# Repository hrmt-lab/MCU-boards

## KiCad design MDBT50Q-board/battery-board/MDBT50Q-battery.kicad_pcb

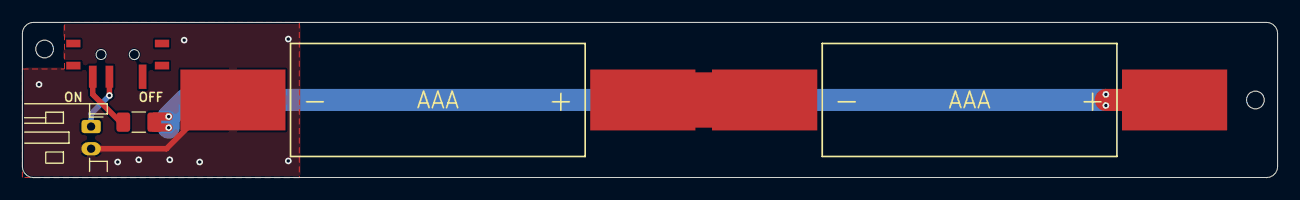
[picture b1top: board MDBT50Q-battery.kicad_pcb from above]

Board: 2 copper layers, 113.3 x 14.0 mm, 9 parts (0 on the bottom side), 5 nets.

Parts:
BT1, BT3: AAA-; BatteryClip_MYOUNG_MY-AAA-19-J
BT2, BT4: AAA+; BatteryClip_MYOUNG_MY-AAA-20-J
F1: 1206L075SLYR; Fuse_1206_3216Metric
H7, H8: M1.4
J9: Conn_01x02; JST_PH_S2B-PH-K_1x02_P2.00mm_Horizontal_CornerSilk
SW2: SW_SPDT; TGSW_MK12C02

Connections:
/BATT_P: BT4.1, F1.1
/CELL_MID: BT2.1, BT3.1
BATT_GND: BT1.1, J9.2
BATT_SW: J9.1, SW2.2
unnamed: F1.2, SW2.3

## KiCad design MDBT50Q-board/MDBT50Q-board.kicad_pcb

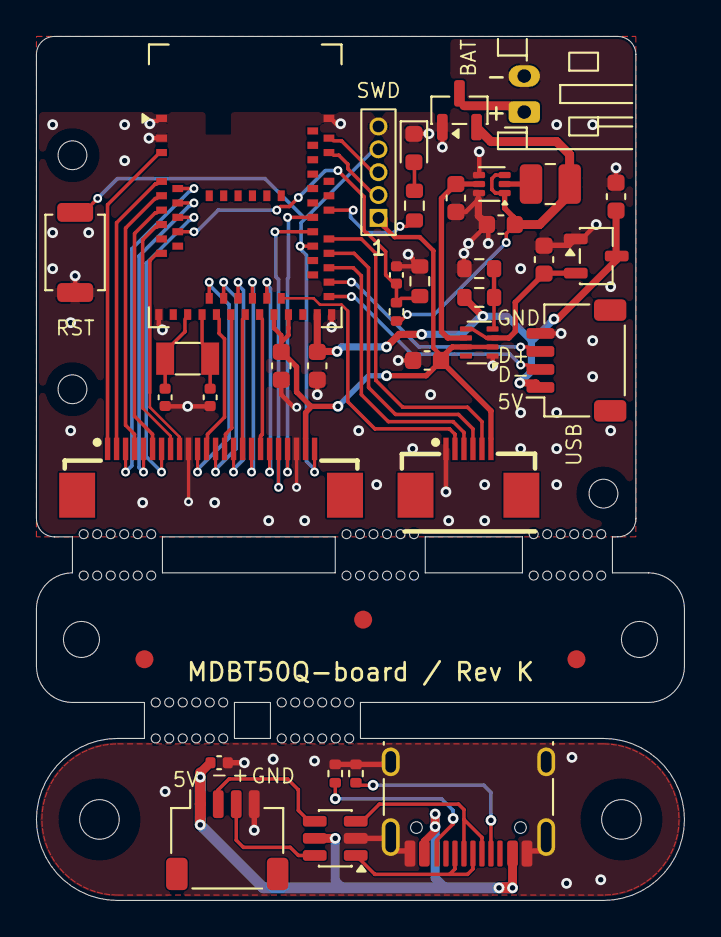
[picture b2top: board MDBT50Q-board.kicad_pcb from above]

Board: 2 copper layers, 36.0 x 48.0 mm, 105 parts (0 on the bottom side), 51 nets.

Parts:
C1, C7, C9, C11: 10μF; C_0603_1608Metric
C2, C6: 4.7μF; C_0603_1608Metric
C3, C8: 100nF; C_0402_1005Metric
C4, C5: 12pF; C_0402_1005Metric
C10: 22μF; C_0603_1608Metric
D1: KT-0603R; LED_0603_1608Metric
FID1, FID2, FID3: Fiducial_1mm_Mask2mm
H1, H2, H3: M1.4
H5, H6: NPTH
J1: USB_C_Receptacle_USB2.0_16P; USB_C_Receptacle_HRO_TYPE-C-31-M-12_Edge1p3mm
J2, J4: Conn_01x04; JST_SH_SM04B-SRSS-TB_1x04-1MP_P1.00mm_Horizontal
J3: Conn_01x05; PinHeader_1x05_P1.27mm_Vertical
J6: Conn_01x24; FPC-SMD_24P-P0.50_FPC-05F-24PH20
J7: Conn_01x06; FPC-SMD_6P-P0.50_XUNPU_FPC-05F-6PH20
J8: Conn_01x02; JST_PH_S2B-PH-K_1x02_P2.00mm_Horizontal_CornerSilk
L1: 1μH; L_1008_2520Metric
MB1, MB2, MB3, MB4, MB5, MB6, MB7, MB8, MB9, MB10, MB11, MB12, MB13, MB14, MB15, MB16, MB17, MB18, MB19, MB20, MB21, MB22, MB23, MB24, MB25, MB26, MB27, MB28, MB29, MB30, MB31, MB32, MB33, MB34, MB35, MB36, MB37, MB38, MB39, MB40, MB41, MB42, MB43, MB44, MB45, MB46, MB47, MB48, MB49, MB50, MB51, MB52, MB53, MB54, MB55, MB56, MB57, MB58, MB59, MB60: NPTH
Q1: Si2329DS-T1-GE3; SOT-23
R1, R2: 5.1kΩ; R_0402_1005Metric
R3: 1.0MΩ; R_0402_1005Metric
R4: 470kΩ; R_0603_1608Metric
R5: 27kΩ; R_0603_1608Metric
R6: 10kΩ; R_0603_1608Metric
R7: 2.2kΩ; R_0603_1608Metric
SW1: SW_PUSH; SW_SPST_TS-1088-xR020
TOOL1, TOOL2: NPTH
U1: MDBT50Q-P1MV2; Raytac_MDBT50Q
U2: USBLC6-2SC6; SOT-23-6
U3: XC6206P332MR-G; SOT-23-3
U4: TPS61299DRLR; SOT-563
U5: TPS2116DRL; SOT-583-8
Y1: 32.768kHz; Crystal_SMD_3215-2Pin_3.2x1.5mm

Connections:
BAT_3.3V: C10.1, U4.5, U5.6
BAT_MON: C8.1, R3.2, R4.1, U1.11
DBG_LED: R7.1, U1.44
GND: C1.2, C2.2, C4.2, C5.2, C6.2, C7.2, C8.2, C9.2, C10.2, C11.2, D1.1, J2.4, J3.5, J6.10, J6.22, J7.1, J8.2, Q1.1, R4.2, R6.2, SW1.2, U1.1, U1.2, U1.15, U1.33, U1.55, U3.1, U4.4, U4.6, U5.1
unnamed: D1.2, R7.2
unnamed: J1.A5, R2.1
unnamed: J1.B5, R1.1
unnamed: J1.A6, J1.B6, U2.1
unnamed: J1.A7, J1.B7, U2.3
unnamed: C9.1, L1.1, Q1.2, R3.1, U4.1, U4.3
unnamed: C4.1, U1.17, Y1.2
unnamed: C5.1, U1.18, Y1.1
unnamed: L1.2, U4.2
unnamed: R5.2, R6.1, U5.4
P0.03: J6.7, U1.9
P0.04: J6.12, U1.20
P0.05: J6.13, U1.21
P0.06: J6.14, U1.22
P0.07: J6.15, U1.23
P0.08: J6.16, U1.24
P0.11: J6.19, U1.27
P0.12: J7.2, U1.29
P0.13: J7.3, U1.37
P0.15: J7.4, U1.39
P0.17: J7.5, U1.41
P0.19: J6.20, U1.42
P0.21: J6.21, U1.43
P0.26: J6.11, U1.19
P0.29: J6.8, U1.10
P0.30: J6.9, U1.14
P1.08: J6.17, U1.25
P1.09: J6.18, U1.26
P1.10: J6.1, U1.3
P1.11: J6.2, U1.4
P1.12: J6.3, U1.5
P1.13: J6.4, U1.6
P1.14: J6.5, U1.7
P1.15: J6.6, U1.8
RESET: J3.4, J6.24, SW1.1, U1.40
SWDCLK: J3.3, U1.53
SWDIO: J3.2, U1.51
SYS_3V3: C1.1, C11.1, J3.1, J6.23, J7.6, U1.28, U1.30, U5.2, U5.7
USB_3.3V: C7.1, U3.2, U5.3, U5.5
USB_5V: C2.1, C6.1, J2.1, R5.1, U1.32, U3.3
USB_DM: J2.2, U1.34
USB_DP: J2.3, U1.35
USB_PORT_5V: C3.1, J1.A4, J1.A9, J1.B4, J1.B9, J4.1, U2.5
USB_PORT_DM: J4.2, U2.4
USB_PORT_DP: J4.3, U2.6
USB_PORT_GND: C3.2, J1.A1, J1.A12, J1.B1, J1.B12, J1.SH, J4.4, R1.2, R2.2, U2.2
VBAT_IN: J8.1, Q1.3

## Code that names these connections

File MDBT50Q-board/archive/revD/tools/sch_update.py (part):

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    s = move_symbol(s, "#FLG02", 93.98, -31.75)                         # -> (285.75, 133.35)
    s = s.replace("(at 239.776 154.178 0)", "(at 247.396 154.178 0)")  # "Reverse polarity protection" heading out of the box
    add = ""
    add += glabel("BATT_GND", 196.85, 165.1, 180)                      # J5 pin 2
    add += wire(229.87, 167.64, 229.87, 172.72) + glabel("BATT_SW", 229.87, 172.72, 180)
    add += conn2("J9", 213.36, 185.42)
    add += glabel("BATT_SW", 208.28, 185.42, 180) + glabel("BATT_GND", 208.28, 187.96, 180)
    add += ('\t(rectangle (start 175.26 149.86) (end 230.6 193.04) (stroke (width 0) (type default)) (fill (type none)) (uuid "%s"))\n' % U("box"))
    add += text("Battery board (separate PCB): J5, F1, SW2, J9", 179.07, 151.765)
    add += text("J9: JST SH 2P to MCU board J8", 179.07, 191.135)
    # --- MCU board: Q1 drain from J8
    add += wire(232.41, 165.1, 232.41, 180.34) + glabel("VBAT_IN", 232.41, 180.34, 270)
    add += conn2("J8", 299.72, 125.73)
    add += glabel("VBAT_IN", 294.64, 125.73, 180)
    add += wire(294.64, 128.27, 292.1, 128.27) + wire(292.1, 128.27, 292.1, 133.35) + wire(292.1, 133.35, 292.1, 135.89)
    add += wire(285.75, 133.35, 292.1, 133.35)
    add += '\t(junction (at 292.1 133.35) (diameter 0) (color 0 0 0 0) (uuid "%s"))\n' % U("jJ8")
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
def rev_d(s):
    s = remove_symbol(s, "J5")
    s = remove_block(s, '(global_label "BATT_GND" (shape passive) (at 196.85 165.1 180)')
    s = remove_block(s, '(text "基板のシルクに')
    s = s.replace("Battery board (separate PCB): J5, F1, SW2, J9", "Battery board (separate PCB): 2x AAA clips BT1-BT4, F1, SW2, J9")
    s = s.replace("(rectangle (start 175.26 149.86)", "(rectangle (start 167.64 149.86)")
    i = s.index("(lib_symbols") + len("(lib_symbols")
    s = s[:i] + "\n" + lib_block("Device.kicad_sym", "Battery_Cell") + lib_block("Connector_Generic.kicad_sym", "Conn_01x01") + s[i:]
    add = ""
    # cell chain: BATT_GND - BAT1 - CELL_MID - BAT2 - BATT_P (= old J5 pin 1, wire to F1 kept)
    add += cell("BAT1", 176.53) + cell("BAT2", 194.31)
    add += wire(181.61, ROW, 191.77, ROW)
    add += glabel("BATT_GND", 173.99, ROW, 90)
    for ref, (x, value, fp, lcsc, mpn, descr) in CLIP.items():
        add += clip(ref, x, value, fp, lcsc, mpn, descr) + wire(x, ROW, x, CLIP_Y - 5.08) + junction(x, ROW)
    add += label("CELL_MID", 181.61, 169.545, 0) + label("BATT_P", 199.39, 169.545, 180)
    add += text("BT1,BT3: MY-AAA-19-J (-) C6937104" + NL + "BT2,BT4: MY-AAA-20-J (+) C6937107" + NL + "2x AAA in series. NO LiPo.", 169.545, 182.88)
    i = s.rindex(")")
    return s[:i] + add + s[i:]
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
